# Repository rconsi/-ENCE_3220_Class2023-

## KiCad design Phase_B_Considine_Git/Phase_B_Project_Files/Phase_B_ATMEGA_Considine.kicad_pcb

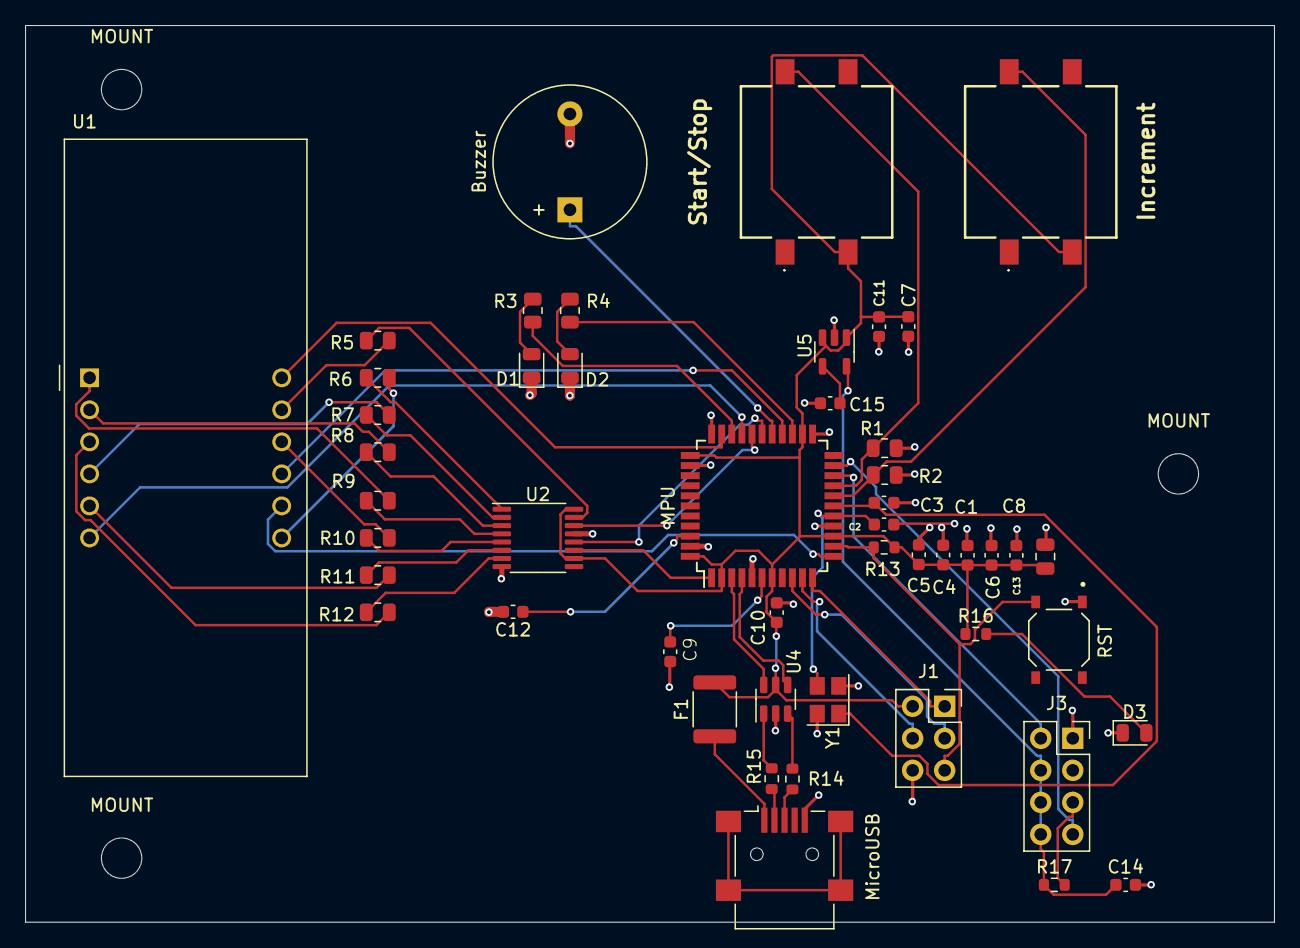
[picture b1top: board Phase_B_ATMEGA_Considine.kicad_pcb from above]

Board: 2 copper layers, 99.1 x 71.1 mm, 52 parts (0 on the bottom side), 53 nets.

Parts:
Buzzer: Speaker; Buzzer_12x9.5RM7.6
C1: 0.1u; C_0603_1608Metric
C2, C3: 22p; C_0603_1608Metric
C4, C5, C6, C7, C10, C11, C12: 0.1uF; C_0603_1608Metric
C8: 10uF; C_0805_2012Metric
C9, C13: 1uF; C_0603_1608Metric
C14: 2.2uF; C_0603_1608Metric
C15: 10nF; C_0603_1608Metric
D1, D2, D3: LED; LED_0805_2012Metric
F1: PTCSMD; Fuse_1812_4532Metric
Increment: PTS125SM43SMTR21M_LFS; PTS125_SMD_Button
J1: AVR-ISP-6; PinSocket_2x03_P2.54mm_Vertical
J3: ESP_Conn; PinSocket_2x04_P2.54mm_Vertical
MOUNT: MountingHole_3.2mm_M3
MOUNT#2, MOUNT#3: MountingHole_3.2mm_M3
MPU: ATmega32U4-A; TQFP-44_10x10mm_P0.8mm
MicroUSB: USB_B_Mini; USB_Mini-B_Lumberg_2486_01_Horizontal
R1, R2: 10k; R_0805_2012Metric
R3, R4: 330; R_0805_2012Metric
R5, R6, R7, R8, R9, R10, R11, R12: 100; R_0805_2012Metric
R13, R17: 10k; R_0603_1608Metric
R14, R15: 22; R_0603_1608Metric
R16: 1k; R_0603_1608Metric
RST: PTS526_SM08_SMTR2_LFS; PTS526_SMD_Button
Start/Stop: PTS125SM43SMTR21M_LFS; PTS125_SMD_Button
U1: CA56-12EWA
U2: 74HC595; TSSOP-16_4.4x5mm_P0.65mm
U4: USBLC6-2SC6; SOT-23-6
U5: LP2985-3.3; SOT-23-5
Y1: 16MHz; Crystal_SMD_Abracon_ABM8G-4Pin_3.2x2.5mm

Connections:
+3.3V: C14.1, J3.4, J3.6, J3.8, R17.1, U5.5 (VOUT)
+5V: C1.1, C4.1, C5.1, C6.1, C7.1, C8.1, C10.1, C11.1, C13.1, F1.2, Increment.C1 (COM_1), J1.2 (VCC), MPU.2 (UVCC), MPU.7 (VBUS), MPU.14 (VCC), MPU.24 (AVCC), MPU.34 (VCC), MPU.44 (AVCC), R13.1, R16.1, Start/Stop.C1 (COM_1), U2.10 (~SRCLR), U2.16 (VCC), U4.5 (VBUS), U5.1 (VIN), U5.3 (ON/~OFF)
/AREF: C12.1, MPU.42 (AREF)
/UCAP: C9.1, MPU.6 (UCAP)
Button_1: MPU.19 (PD1), R1.1, Start/Stop.B1 (NO_2)
Button_2: Increment.B1 (NO_2), MPU.18 (PD0), R2.1
Buzzer: Buzzer.1, MPU.27 (PD7)
DS: MPU.29 (PB5), U2.14 (SER)
Dig1: MPU.32 (PC7), U1.12 (CA1)
Dig2: MPU.26 (PD6), U1.9 (CA2)
Dig3: MPU.12 (PB7), U1.8 (CA3)
Dig4: MPU.30 (PB6), U1.6 (CA4)
GND: Buzzer.2, C1.2, C2.1, C3.2, C4.2, C5.2, C6.2, C7.2, C8.2, C9.2, C10.2, C11.2, C12.2, C13.2, C14.2, C15.2, D1.1 (K), D2.1 (K), D3.1 (K), J1.6 (GND), J3.1, MPU.5 (UGND), MPU.15 (GND), MPU.23 (GND), MPU.33 (~HWB/PE2), MPU.35 (GND), MPU.43 (GND), MicroUSB.5 (GND), R1.2, R2.2, RST.1, U2.8 (GND), U2.13 (~OE), U4.2 (GND), U5.2 (GND), Y1.2, Y1.4
GREEN_LED: MPU.25 (PD4), R4.1
MISO: J1.1 (MISO), MPU.11 (PB3)
MOSI: J1.4 (MOSI), MPU.10 (PB2)
unnamed: D1.2 (A), R3.2
unnamed: D2.2 (A), R4.2
unnamed: D3.2 (A), R16.2
unnamed: MicroUSB.3 (D+), R14.1
unnamed: MicroUSB.2 (D-), R15.1
unnamed: F1.1, MicroUSB.1 (VBUS)
unnamed: J3.5, R17.2
unnamed: R12.2, U1.3 (DPX)
unnamed: R5.2, U1.11 (a)
unnamed: R6.2, U1.7 (b)
unnamed: R7.2, U1.4 (c)
unnamed: R8.2, U1.2 (d)
unnamed: R9.2, U1.1 (e)
unnamed: R10.2, U1.10 (f)
unnamed: R11.2, U1.5 (g)
unnamed: C15.1, U5.4 (BP)
RED_LED: MPU.31 (PC6), R3.1
RST: J1.5 (~RST), MPU.13 (~RESET), R13.2, RST.3
RX: J3.7, MPU.21 (PD3)
SCK: J1.3 (SCK), MPU.9 (PB1)
SH_CP: MPU.1 (PE6), U2.11 (SRCLK)
ST_CP: MPU.28 (PB4), U2.12 (RCLK)
TX: J3.2, MPU.20 (PD2)
USB_CONN_D+: R14.2, U4.3 (I/O2)
USB_CONN_D-: R15.2, U4.1 (I/O1)
USB_D+: MPU.4 (D+), U4.4 (I/O2)
USB_D-: MPU.3 (D-), U4.6 (I/O1)
XTAL1: C2.2, MPU.17 (XTAL1), Y1.1
XTAL2: C3.1, MPU.16 (XTAL2), Y1.3
a: R5.1, U2.15 (QA)
b: R6.1, U2.1 (QB)
c: R7.1, U2.2 (QC)
d: R8.1, U2.3 (QD)
dp: R12.1, U2.7 (QH)
e: R9.1, U2.4 (QE)
f: R10.1, U2.5 (QF)
g: R11.1, U2.6 (QG)

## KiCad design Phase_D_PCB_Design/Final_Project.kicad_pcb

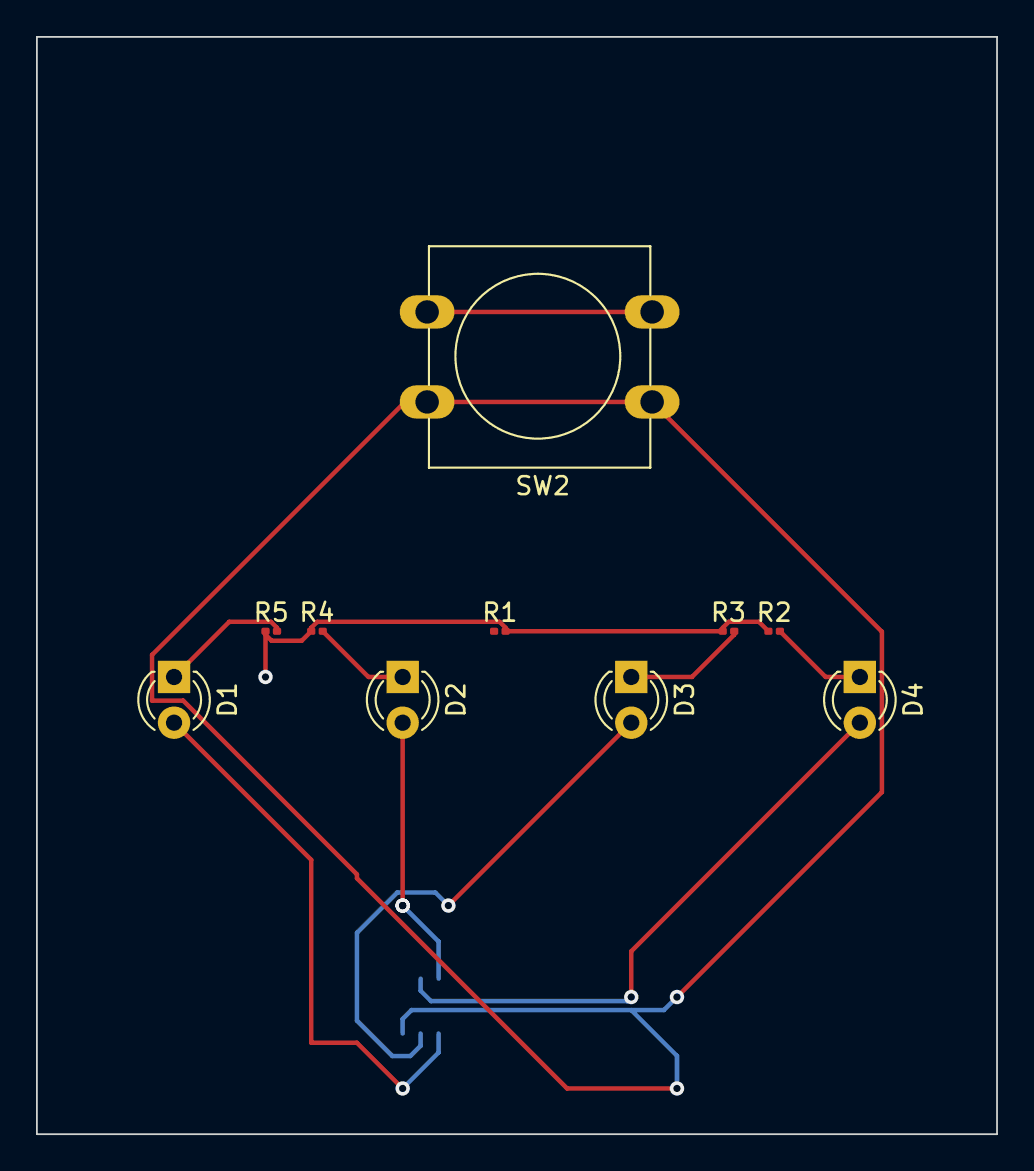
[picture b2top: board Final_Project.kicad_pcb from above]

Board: 2 copper layers, 53.3 x 61.0 mm, 11 parts (1 on the bottom side), 10 nets.

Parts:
D1, D2, D3, D4: LED; LED_D3.0mm
J1: Conn_02x10_Odd_Even; PinSocket_2x10_P1.00mm_Vertical_SMD
R1: 1k; R_0201_0603Metric
R2, R3, R4, R5: 330; R_0201_0603Metric
SW2: SW_MEC_5E; SW_PUSH-12mm

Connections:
GND: R1.2, R2.1, R3.1, R4.1, R5.1
unnamed: D1.1 (K), R5.2
unnamed: D2.1 (K), R4.2
unnamed: D3.1 (K), R3.2
unnamed: D4.1 (K), R2.2
PA4: D1.2 (A), J1.16
PA5: D2.2 (A), J1.15
PA6: D3.2 (A), J1.18
PA7: D4.2 (A), J1.17
PC4: J1.20, SW2.1

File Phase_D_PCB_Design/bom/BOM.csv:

"#","Reference","Qty","Value","Footprint","DNP"
"1","D1, D2, D3, D4","4","LED","LED_THT:LED_D3.0mm",""
"2","J1","1","Conn_02x10_Odd_Even","Connector_PinSocket_1.00mm:PinSocket_2x10_P1.00mm_Vertical_SMD",""
"3","R1","1","1k","Resistor_SMD:R_0201_0603Metric",""
"4","R2, R3, R4, R5","4","330","Resistor_SMD:R_0201_0603Metric",""
"5","SW2","1","SW_MEC_5E","Button_Switch_THT:SW_PUSH-12mm",""
"6","U1","1","STM32F401VBTx","Package_QFP:LQFP-100_14x14mm_P0.5mm",""

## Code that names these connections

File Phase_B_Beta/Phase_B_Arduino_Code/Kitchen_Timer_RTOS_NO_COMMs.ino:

// Include Arduino FreeRTOS library
#include <Arduino_FreeRTOS.h>

#define BUTTON_2  2  // Inc Timer
#define BUTTON_1  3  // Start/Stop Timer and Stop Buzzer
#define GREEN_LED 4
#define RED_LED   5
#define BUZZER    6

#define DATA      9 // DS
#define LATCH     8 // ST_CP
#define CLOCK     7 // SH_CP

#define DIGIT_4   10
#define DIGIT_3   11
#define DIGIT_2   12
#define DIGIT_1   13

// 7-Seg Display Variables
unsigned char gTable[]=
{0x3f,0x06,0x5b,0x4f,0x66,0x6d,0x7d,0x07,0x7f,0x6f,0x77,0x7c
,0x39,0x5e,0x79,0x71,0x00};

// Timer Variables
#define DEFAULT_COUNT 30     // default value is 30secs
int  gCount = DEFAULT_COUNT;

char gBuzzerFlag = 0;
unsigned char gTimerRunning = 0;

//define task handles
TaskHandle_t TaskClockTimer_Handler;

void setup() {

  /**
   * Set up Pins
   */
   // LEDs Pins
   pinMode(RED_LED, OUTPUT);
   pinMode(GREEN_LED, OUTPUT);

   // LEDs -> Timer Stopped
   digitalWrite(RED_LED, HIGH);
   digitalWrite(GREEN_LED, HIGH);
  
   // Button Pins
   pinMode(BUTTON_1, INPUT);
   pinMode(BUTTON_2, INPUT);
  
   // Buzer Pins
   pinMode(BUZZER, OUTPUT);
  
   // Buzzer -> Off
   digitalWrite(BUZZER,LOW);
  
   // 7-Seg Display
   pinMode(DIGIT_1, OUTPUT);
   pinMode(DIGIT_2, OUTPUT);
   pinMode(DIGIT_3, OUTPUT);
   pinMode(DIGIT_4, OUTPUT);
  
   // Shift Register Pins
   pinMode(LATCH, OUTPUT);
   pinMode(CLOCK, OUTPUT);
   pinMode(DATA, OUTPUT);

  dispOff();  // turn off the display

  // 7-Seg Display Task -> Running time 5 ms
  xTaskCreate(TaskDisplay, // Task function
              "Display", // A name just for humans
              128,  // This stack size can be checked & adjusted by reading the Stack Highwater
              NULL, 
              0, // Priority, with 3 (configMAX_PRIORITIES - 1) being the highest, and 0 being the lowest.
              NULL);

  // Clock timer Task -> Running time 1 second
  xTaskCreate(TaskClockTimer, // Task function
              "ClockTimer", // Task name
              128,  // Stack size
              NULL, 
              0, // Priority
              &TaskClockTimer_Handler);

  stopTaskClockTimer();

  // Buzzer Task -> Running at 250 ms
  xTaskCreate(TaskBuzzer, // Task function
              "Buzzer", // Task name
              128, // Stack size 
              NULL, 
              0, // Priority
              NULL );

  // Read Button 2 Task -> Running at 10 ms
  xTaskCreate(TaskReadButton2, // Task function
              "ReadButton2", // Task name
              128,  // Stack size
              NULL, 
              0, // Priority
              NULL);

  // Read Button 1 Task -> Running at 10 ms
  xTaskCreate(TaskReadButton1, // Task function
              "ReadButton1", // Task name
              128,  // Stack size
              NULL, 
              0, // Priority
              NULL);
}

void loop() {}

// ------
// TASKS
// ------

/**
 * 7-Seg Display Task
 * Refresh display -> Running at 5 ms
 */
void TaskDisplay(void * pvParameters) {
  (void) pvParameters;

  byte current_digit;
  
  for (;;) 
  {
    dispOff();  // turn off the display
   
    switch (current_digit)
    {
      case 1: //0x:xx
        display( int((gCount/60) / 10) % 6, 0 );   // prepare to display digit 1 (most left)
        digitalWrite(DIGIT_1, LOW);  // turn on digit 1
        break;
   
      case 2: //x0:xx
        display( int(gCount / 60) % 10, 1 );   // prepare to display digit 2
        digitalWrite(DIGIT_2, LOW);     // turn on digit 2
        break;
   
      case 3: //xx:0x
        display( (gCount / 10) % 6, 0 );   // prepare to display digit 3
        digitalWrite(DIGIT_3, LOW);    // turn on digit 3
        break;
   
      case 4: //xx:x0
        display(gCount % 10, 0); // prepare to display digit 4 (most right)
        digitalWrite(DIGIT_4, LOW);  // turn on digit 4
    }
   
    current_digit = (current_digit % 4) + 1;

    // 5 ms
    vTaskDelay( 5 / portTICK_PERIOD_MS );
  }
}

/**
 * Clock Timer Task
 * If timer is on, decrements timer by one second.
 */
void TaskClockTimer(void *pvParameters)
{
  (void) pvParameters;
  
  for (;;)
  {
    gCount--;

    if(gCount == 0)
    { 
      //raise alarm
      gBuzzerFlag = 1;
      gTimerRunning = 0;

      //stop timer
      stopTaskClockTimer();
    }

    // 1 second
    vTaskDelay( 1000 / portTICK_PERIOD_MS );
  }
}
void TaskBuzzer(void *pvParameters)
{
  (void) pvParameters;

  unsigned char state = 0;

  for (;;)
  {
    // Attend gBuzzerFlag
    if(gBuzzerFlag == 1)
    {      
      // Make Noise...
      digitalWrite(RED_LED, HIGH);
      digitalWrite(GREEN_LED, LOW);
      
      digitalWrite(BUZZER, HIGH);
      vTaskDelay( 250 / portTICK_PERIOD_MS );
      digitalWrite(BUZZER, LOW);
      vTaskDelay( 250 / portTICK_PERIOD_MS );
    }
    else
      digitalWrite(BUZZER, LOW);

    // One tick delay (15ms) in between reads for stability
    vTaskDelay(1);
  }
}


void TaskReadButton2(void *pvParameters)
{
  (void) pvParameters;
  unsigned int buttonState = 0;  // variable for reading the pushbutton status
  
  for (;;)
  { 
    // Read Button 2 -> pooling method is fine in this case
    buttonState = digitalRead(BUTTON_2);

    // TODO -> implement the code to debounce the button
    if(buttonState == 1)
    {
      vTaskDelay( 250 / portTICK_PERIOD_MS );  // Very simple debounce
      
      gCount++;
    }

    // One tick delay (15ms) in between reads for stability
    vTaskDelay(1);
  }
}


void TaskReadButton1(void *pvParameters)
{
  (void) pvParameters;

  unsigned int buttonState = 0;  // variable for reading the pushbutton status
  
  for (;;)
  { 
    // Read Button 1 -> pooling method is fine in this case
    buttonState = digitalRead(BUTTON_1);

    if(buttonState == 1)
    {
      vTaskDelay( 250 / portTICK_PERIOD_MS );  // Very simple debounce
      
      if(gTimerRunning == 0)
      {
        // Start Clock Timer
        gTimerRunning = 1;
  
        if(gCount == 0)
        {
          gCount = DEFAULT_COUNT;
        }
  
        if(gBuzzerFlag == 1)
        {
          gBuzzerFlag = 0;
  
          // LEDs -> Timer Stopped
          digitalWrite(RED_LED, HIGH);
          digitalWrite(GREEN_LED, HIGH);
        }
        else
        {
          startTaskClockTimer();
          // LEDs -> Timer Running
          digitalWrite(RED_LED, LOW);
          digitalWrite(GREEN_LED, HIGH);
        }
      }
      else
      {
        // Stop Timer
        stopTaskClockTimer();
        gTimerRunning = 0;
  
        // LEDs -> Timer Running
        digitalWrite(RED_LED, HIGH);
        digitalWrite(GREEN_LED, HIGH);
      }
    }

    // One tick delay (15ms) in between reads for stability
    vTaskDelay(1);
  }
}

// --------------------------------------------------

void stopTaskClockTimer()
{
  vTaskSuspend(TaskClockTimer_Handler);
}

void startTaskClockTimer()
{
  vTaskResume(TaskClockTimer_Handler);
}

void dispOff()
{
   digitalWrite(DIGIT_1, HIGH);
   digitalWrite(DIGIT_2, HIGH);
   digitalWrite(DIGIT_3, HIGH);
   digitalWrite(DIGIT_4, HIGH);
}

void display(unsigned char num, unsigned char dp)
{
  digitalWrite(LATCH, LOW);
  shiftOut(DATA, CLOCK, MSBFIRST, gTable[num] | (dp<<7));
  digitalWrite(LATCH, HIGH);
}

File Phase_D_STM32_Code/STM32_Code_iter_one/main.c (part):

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  GPIO_InitStruct.Pull = GPIO_NOPULL;
  HAL_GPIO_Init(GPIOA, &GPIO_InitStruct);

  /*Configure GPIO pins : PA4 PA5 PA6 PA7 */
  GPIO_InitStruct.Pin = GPIO_PIN_4|GPIO_PIN_5|GPIO_PIN_6|GPIO_PIN_7;
  GPIO_InitStruct.Mode = GPIO_MODE_OUTPUT_PP;
  GPIO_InitStruct.Pull = GPIO_NOPULL;
  GPIO_InitStruct.Speed = GPIO_SPEED_FREQ_LOW;
  HAL_GPIO_Init(GPIOA, &GPIO_InitStruct);

  /*Configure GPIO pin : PC4 */
  GPIO_InitStruct.Pin = GPIO_PIN_4;
  GPIO_InitStruct.Mode = GPIO_MODE_OUTPUT_PP;
  GPIO_InitStruct.Pull = GPIO_NOPULL;
  GPIO_InitStruct.Speed = GPIO_SPEED_FREQ_LOW;
  HAL_GPIO_Init(GPIOC, &GPIO_InitStruct);

  /*Configure GPIO pins : PB1 BOOT1_Pin */
  GPIO_InitStruct.Pin = GPIO_PIN_1|BOOT1_Pin;
  GPIO_InitStruct.Mode = GPIO_MODE_INPUT;
  GPIO_InitStruct.Pull = GPIO_NOPULL;
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
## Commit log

2023-04-06 Add files via upload
    Initial Kitchen Timer Attempt
2023-04-06 Add files via upload
    Kitchen Timer Iteration 2 , also not working
2023-04-06 Add files via upload
    Kitchen Timer iteration 3, buzzer works, counter works, and the LEDs are properly working, however the 7-segment display is still experiencing issues
2023-06-01 Create Phase_D

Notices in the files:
Phase_D_STM32_Code/STM32_Code_iter_one/main.c:
Copyright (c) 2023 STMicroelectronics.
All rights reserved.
This software is licensed under terms that can be found in the LICENSE file
